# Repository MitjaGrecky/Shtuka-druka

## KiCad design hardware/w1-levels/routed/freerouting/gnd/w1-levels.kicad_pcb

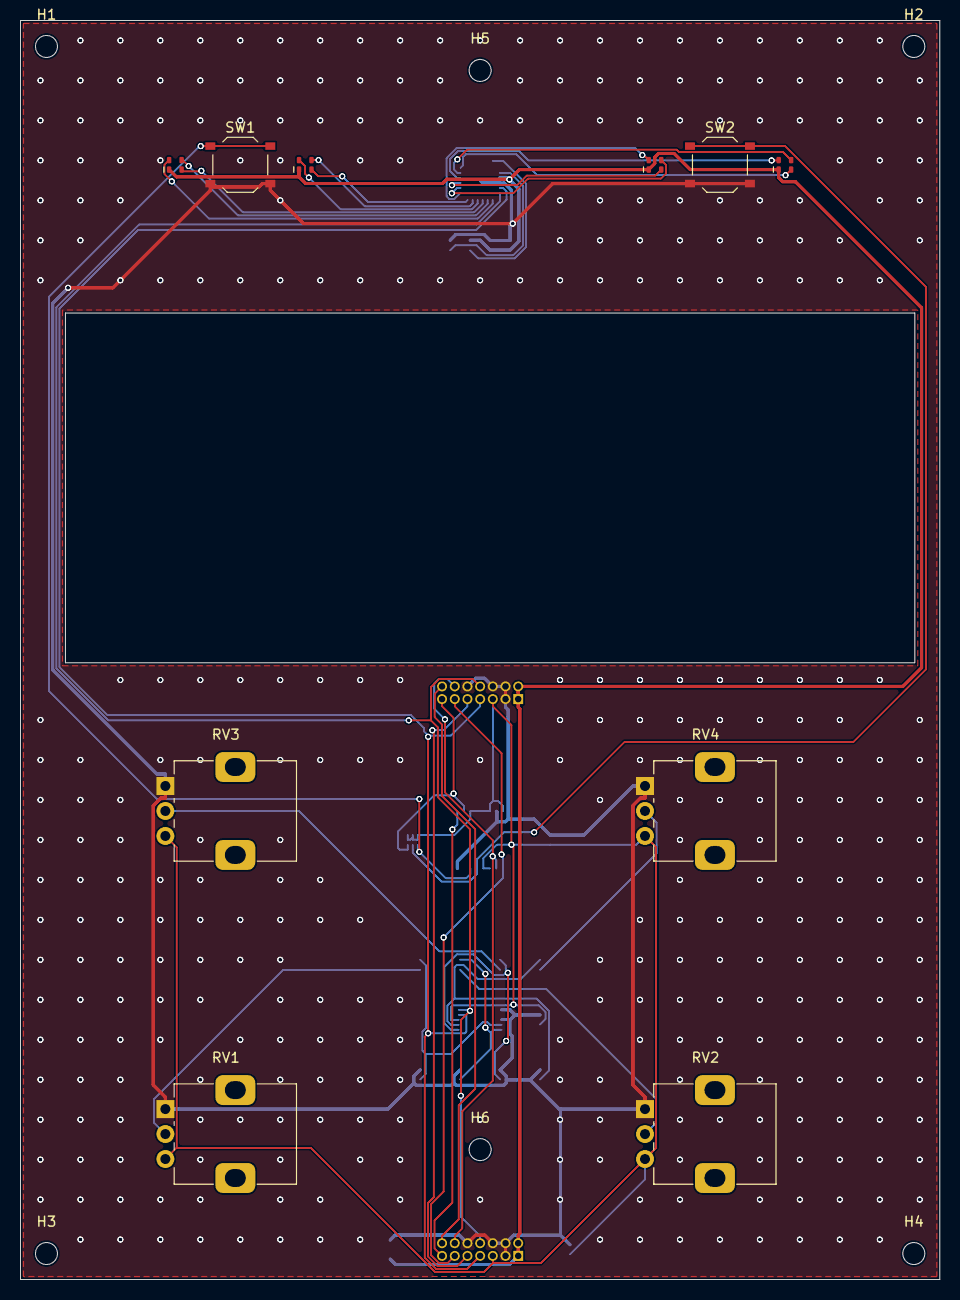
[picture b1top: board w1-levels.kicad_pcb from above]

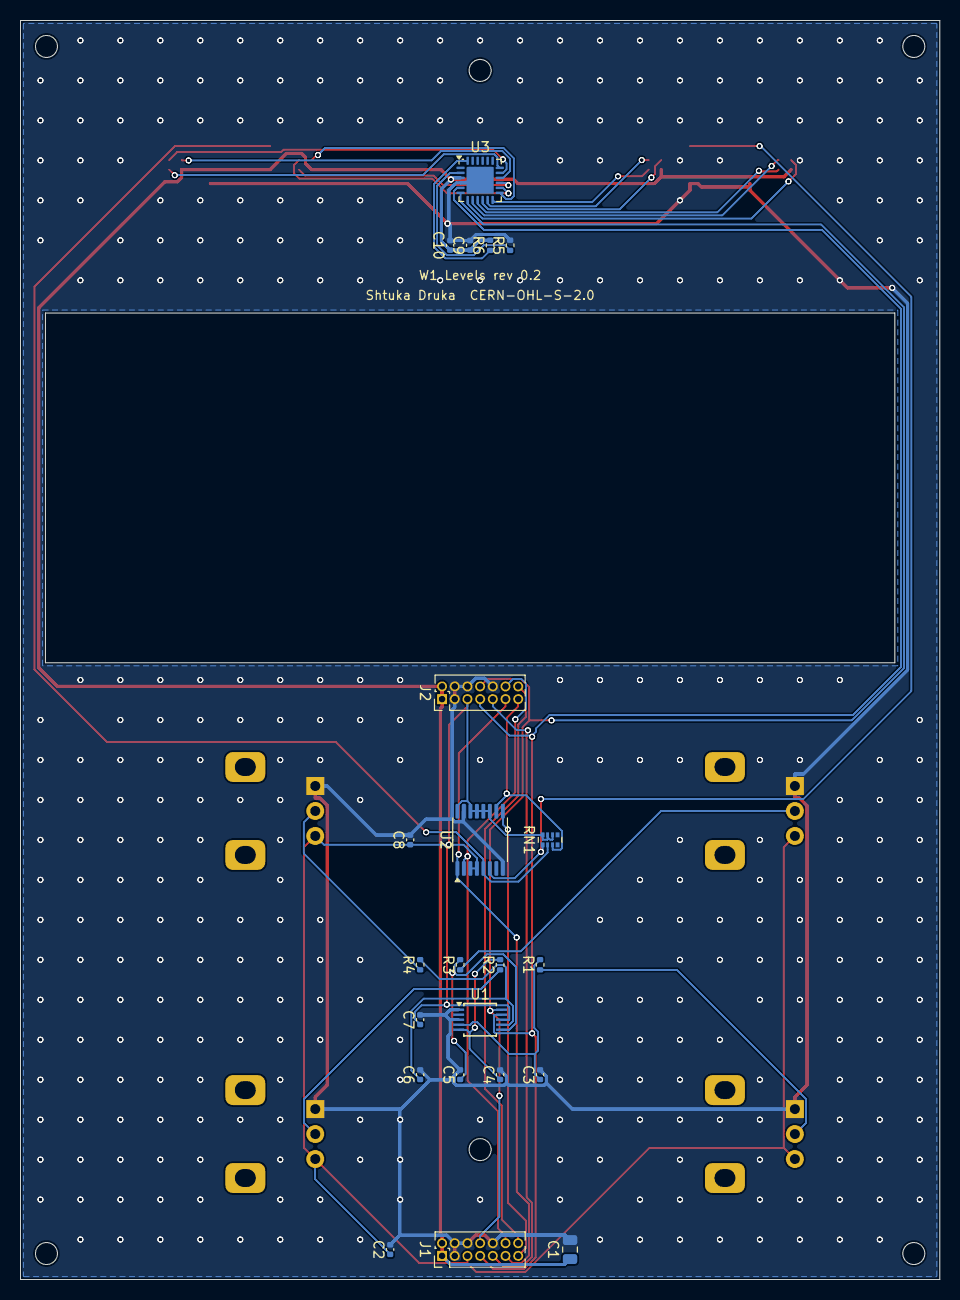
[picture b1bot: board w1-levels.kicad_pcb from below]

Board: 2 copper layers, 92.0 x 126.0 mm, 38 parts (22 on the bottom side), 35 nets.

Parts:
C1: 10u; C_0805_2012Metric
C2, C9: 1u; C_0402_1005Metric
C3, C4, C5, C6, C7, C8, C10: 100n; C_0402_1005Metric
D1, D2, D3, D4: XL-1615RGBC-RF; LED_RGB_XL-1615RGBC_1.6x1.5mm
H1, H2, H3, H4, H5, H6: M2; MountingHole_2.2mm_M2
J1: Bus to P1 2x7 1.27; PinHeader_2x07_P1.27mm_Vertical
J2: Bus to M5 2x7 1.27; PinHeader_2x07_P1.27mm_Vertical
R1, R2, R3, R4: 1k; R_0402_1005Metric
R5: 4.7k; R_0402_1005Metric
R6: 10k; R_0402_1005Metric
RN1: 4x10k; R_Array_Convex_4x0402
RV1, RV2, RV3, RV4: 10k lin, end stops; Potentiometer_Alps_RK09K_Single_Vertical
SW1, SW2: TS-1187A-B-A-B; SW_Push_1P1T_XKB_TS-1187A
U1: ADS1115IDGSR; TSSOP-10_3x3mm_P0.5mm
U2: 74HC165PW; TSSOP-16_4.4x5mm_P0.65mm
U3: IS31FL3218-QFLS2-TR; QFN-24-1EP_4x4mm_P0.5mm_EP2.7x2.7mm

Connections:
+3V3: C2.1, C7.1, C8.1, J1.5, J2.5, RN1.6, RN1.7, RN1.8, RV1.3, RV2.3, RV3.3, RV4.3, U1.8, U2.3, U2.4, U2.11, U2.12, U2.13, U2.14, U2.16
+5V: C1.1, C9.1, C10.1, D1.2, D2.2, D3.2, D4.2, J1.1, J1.2, J2.1, J2.2, R6.2, U3.3
/AIN0: C3.1, R1.2, U1.4
/AIN1: C4.1, R2.2, U1.5
/AIN2: C5.1, R3.2, U1.6
/AIN3: C6.1, R4.2, U1.7
/BTN1: RN1.1, SW1.1, U2.6
/BTN2: RN1.2, SW2.1, U2.5
/OUT1: D1.1, U3.7
/OUT2: D1.3, U3.8
/OUT3: D1.4, U3.9
/OUT4: D2.1, U3.10
/OUT5: D2.3, U3.11
/OUT6: D2.4, U3.12
/OUT7: D3.1, U3.13
/OUT8: D3.3, U3.14
/OUT9: D3.4, U3.15
/OUT10: D4.1, U3.16
/OUT11: D4.3, U3.17
/OUT12: D4.4, U3.18
/POT1: R1.1, RV1.2
/POT2: R2.1, RV2.2
/POT3: R3.1, RV3.2
/POT4: R4.1, RV4.2
/REXT: R5.1, U3.2
/SCL: J1.8, J2.8, U1.10, U3.6
/SDA: J1.7, J2.7, U1.9, U3.5
/SDB: R6.1, U3.24
/SR_CLK: J1.12, J2.12, U2.2
/SR_IN: J1.14, J2.14
/SR_M5: J2.13, RN1.3, U2.10
/SR_OUT: J1.13, U2.9
/~INT: J1.9, J2.9
/~SR_LOAD: J1.11, J2.11, U2.1
GND: C1.2, C2.2, C3.2, C4.2, C5.2, C6.2, C7.2, C8.2, C9.2, C10.2, J1.3, J1.4, J1.6, J1.10, J2.3, J2.4, J2.6, J2.10, R5.2, RV1.1, RV2.1, RV3.1, RV4.1, SW1.2, SW2.2, U1.1, U1.3, U2.8, U2.15, U3.4, U3.25

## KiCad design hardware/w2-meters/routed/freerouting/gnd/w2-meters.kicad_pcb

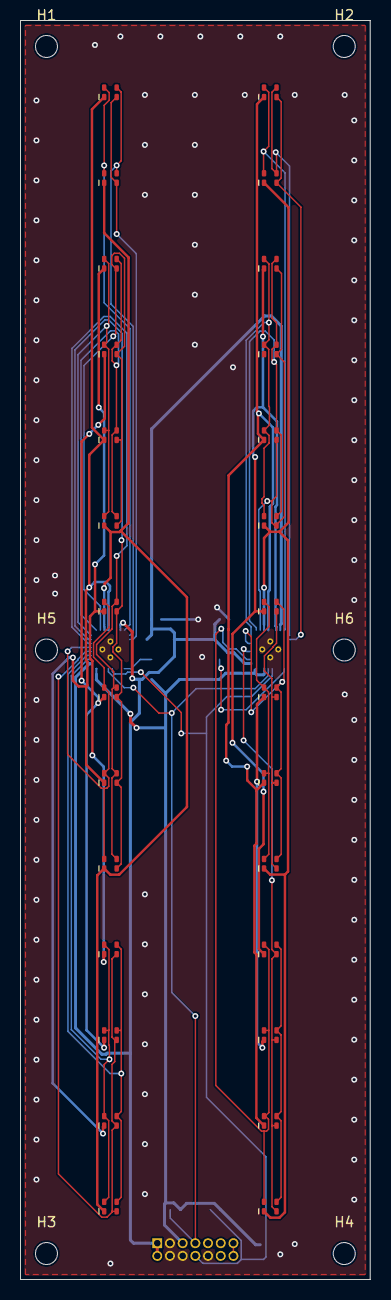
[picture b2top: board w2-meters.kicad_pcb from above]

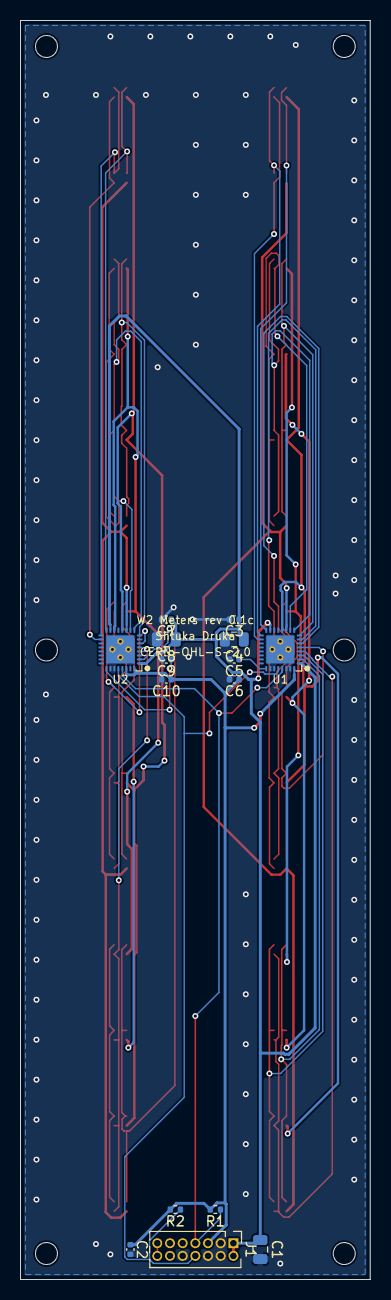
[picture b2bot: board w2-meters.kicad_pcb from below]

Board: 2 copper layers, 35.0 x 126.0 mm, 49 parts (15 on the bottom side), 40 nets.

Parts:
C1: 10u; C_0805_2012Metric
C2, C3, C5, C7, C9: 1u; C_0402_1005Metric
C4, C8: 4.7u; C_0805_2012Metric
C6, C10: 1n; C_0402_1005Metric
D1, D2, D3, D4, D5, D6, D7, D8, D9, D10, D11, D12, D13, D14, D15, D16, D17, D18, D19, D20, D21, D22, D23, D24, D25, D26, D27, D28: XL-1615RGBC-RF; LED_RGB_XL-1615RGBC_1.6x1.5mm
H1, H2, H3, H4, H5, H6: M2; MountingHole_2.2mm_M2
J1: Module bus 2x7 1.27; PinHeader_2x07_P1.27mm_Vertical
R1, R2: 4.7k; R_0402_1005Metric
U1, U2: LP5864RSMR; VQFN-32-1EP_4x4mm_P0.4mm_EP2.8x2.8mm

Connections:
+3V3: C2.1, C6.1, C10.1, J1.5, R1.2, R2.2, U1.32, U2.30, U2.32
+5V: C1.1, C3.1, C4.1, C7.1, C8.1, J1.1, J1.2, U1.1, U1.15, U2.1, U2.15
/L_CS0: D1.1, D2.1, D3.1, D4.1, U1.2
/L_CS1: D1.3, D2.3, D3.3, D4.3, U1.3
/L_CS2: D1.4, D2.4, D3.4, D4.4, U1.4
/L_CS3: D5.1, D6.1, D7.1, D8.1, U1.5
/L_CS4: D5.3, D6.3, D7.3, D8.3, U1.6
/L_CS5: D5.4, D6.4, D7.4, D8.4, U1.7
/L_CS6: D9.1, D10.1, D11.1, D12.1, U1.8
/L_CS7: D9.3, D10.3, D11.3, D12.3, U1.9
/L_CS8: D9.4, D10.4, D11.4, D12.4, U1.10
/L_CS9: D13.1, D14.1, U1.16
/L_CS10: D13.3, D14.3, U1.17
/L_CS11: D13.4, D14.4, U1.18
/L_SW0: D1.2, D5.2, D9.2, D13.2, U1.11
/L_SW1: D2.2, D6.2, D10.2, D14.2, U1.12
/L_SW2: D3.2, D7.2, D11.2, U1.13
/L_SW3: D4.2, D8.2, D12.2, U1.14
/L_VCAP: C5.1, U1.25
/R_CS0: D15.1, D16.1, D17.1, D18.1, U2.2
/R_CS1: D15.3, D16.3, D17.3, D18.3, U2.3
/R_CS2: D15.4, D16.4, D17.4, D18.4, U2.4
/R_CS3: D19.1, D20.1, D21.1, D22.1, U2.5
/R_CS4: D19.3, D20.3, D21.3, D22.3, U2.6
/R_CS5: D19.4, D20.4, D21.4, D22.4, U2.7
/R_CS6: D23.1, D24.1, D25.1, D26.1, U2.8
/R_CS7: D23.3, D24.3, D25.3, D26.3, U2.9
/R_CS8: D23.4, D24.4, D25.4, D26.4, U2.10
/R_CS9: D27.1, D28.1, U2.16
/R_CS10: D27.3, D28.3, U2.17
/R_CS11: D27.4, D28.4, U2.18
/R_SW0: D15.2, D19.2, D23.2, D27.2, U2.11
/R_SW1: D16.2, D20.2, D24.2, D28.2, U2.12
/R_SW2: D17.2, D21.2, D25.2, U2.13
/R_SW3: D18.2, D22.2, D26.2, U2.14
/R_VCAP: C9.1, U2.25
/SCL: J1.8, R2.1, U1.28, U2.28
/SDA: J1.7, R1.1, U1.29, U2.29
/SR_THRU: J1.13, J1.14
GND: C1.2, C2.2, C3.2, C4.2, C5.2, C6.2, C7.2, C8.2, C9.2, C10.2, J1.3, J1.4, J1.6, J1.10, U1.26, U1.27, U1.30, U1.31, U1.33, U2.26, U2.27, U2.31, U2.33

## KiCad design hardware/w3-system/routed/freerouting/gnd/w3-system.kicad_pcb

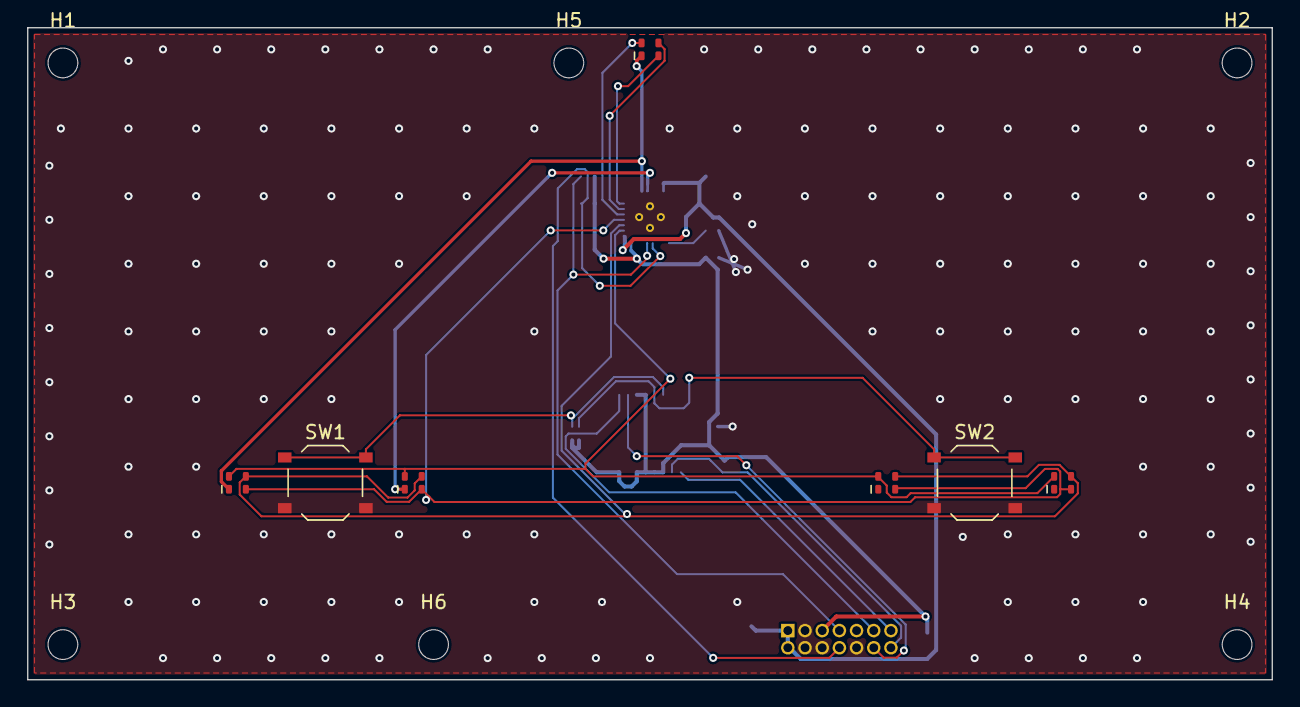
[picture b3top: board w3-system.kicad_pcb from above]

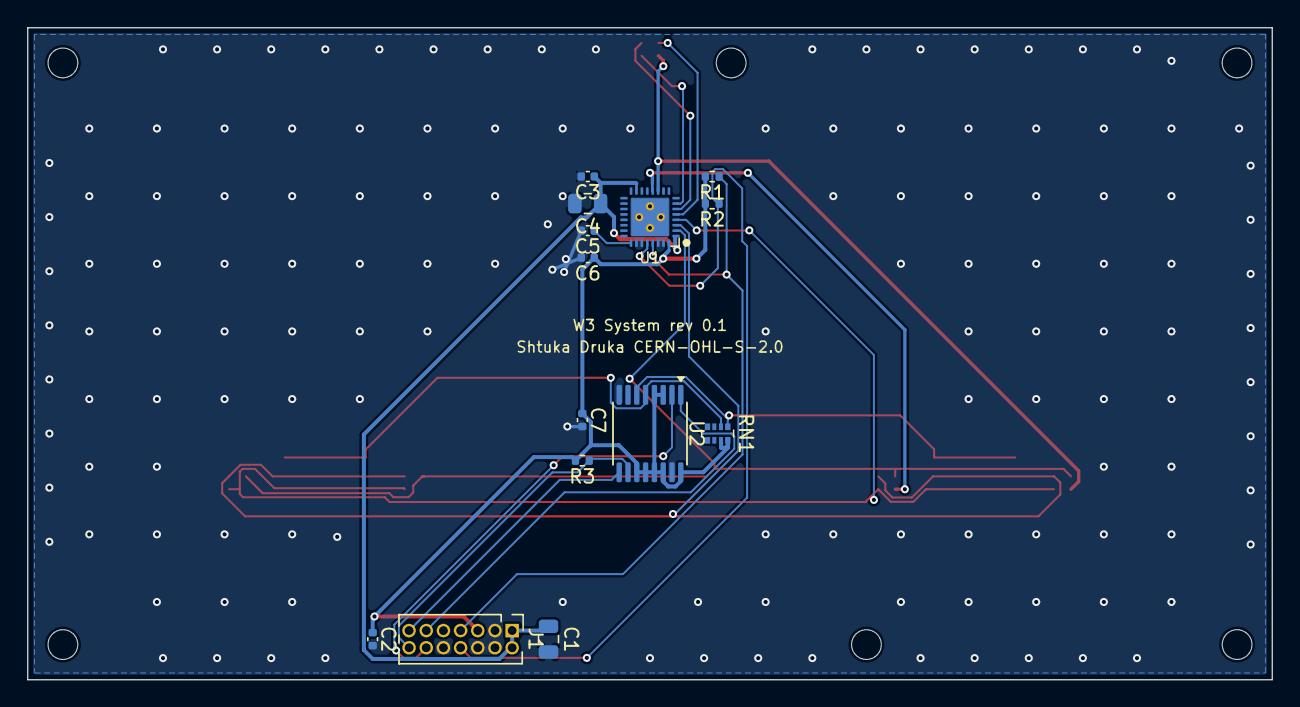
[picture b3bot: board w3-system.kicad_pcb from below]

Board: 2 copper layers, 92.0 x 48.2 mm, 27 parts (14 on the bottom side), 22 nets.

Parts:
C1: 10u; C_0805_2012Metric
C2, C3, C5: 1u; C_0402_1005Metric
C4: 4.7u; C_0805_2012Metric
C6: 1n; C_0402_1005Metric
C7: 100n; C_0402_1005Metric
D1, D2, D3, D4, D5: XL-1615RGBC-RF; LED_RGB_XL-1615RGBC_1.6x1.5mm
H1, H2, H3, H4, H5, H6: M2; MountingHole_2.2mm_M2
J1: Module bus 2x7 1.27; PinHeader_2x07_P1.27mm_Vertical
R1, R2: 4.7k; R_0402_1005Metric
R3: 10k; R_0402_1005Metric
RN1: 4x10k; R_Array_Convex_4x0402
SW1, SW2: TS-1187A-B-A-B; SW_Push_1P1T_XKB_TS-1187A
U1: LP5864RSMR; VQFN-32-1EP_4x4mm_P0.4mm_EP2.8x2.8mm
U2: 74HC165PW; TSSOP-16_4.4x5mm_P0.65mm

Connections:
+3V3: C2.1, C6.1, C7.1, J1.5, R1.2, R2.2, R3.2, RN1.7, RN1.8, U1.32, U2.3, U2.4, U2.11, U2.12, U2.13, U2.14, U2.16
+5V: C1.1, C3.1, C4.1, J1.1, J1.2, U1.1, U1.15
/A_CS0: D1.1, D2.1, D3.1, D4.1, U1.2
/A_CS1: D1.3, D2.3, D3.3, D4.3, U1.3
/A_CS2: D1.4, D2.4, D3.4, D4.4, U1.4
/A_CS3: D5.1, U1.5
/A_CS4: D5.3, U1.6
/A_CS5: D5.4, U1.7
/A_SW0: D1.2, D5.2, U1.11
/A_SW1: D2.2, U1.12
/A_SW2: D3.2, U1.13
/A_SW3: D4.2, U1.14
/A_VCAP: C5.1, U1.25
/BTN_PROJECT: RN1.2, SW2.1, U2.5
/BTN_SAVE: RN1.1, SW1.1, U2.6
/SCL: J1.8, R2.1, U1.28
/SDA: J1.7, R1.1, U1.29
/SR_CLK: J1.12, U2.2
/SR_IN: J1.14, R3.1, U2.10
/SR_OUT: J1.13, U2.9
/~SR_LOAD: J1.11, U2.1
GND: C1.2, C2.2, C3.2, C4.2, C5.2, C6.2, C7.2, J1.3, J1.4, J1.6, J1.10, SW1.2, SW2.2, U1.26, U1.27, U1.30, U1.31, U1.33, U2.8, U2.15

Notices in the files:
hardware/w1-levels/routed/freerouting/gnd/w1-levels.kicad_pcb:
Shtuka Druka - open hardware, CERN-OHL-S-2.0
Shtuka Druka  CERN-OHL-S-2.0
hardware/w2-meters/routed/freerouting/gnd/w2-meters.kicad_pcb:
CERN-OHL-S-2.0
